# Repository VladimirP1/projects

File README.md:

[Crop whitespace from svgs](https://vladimirp1.github.io/projects/svg-cropper/cropper.html)

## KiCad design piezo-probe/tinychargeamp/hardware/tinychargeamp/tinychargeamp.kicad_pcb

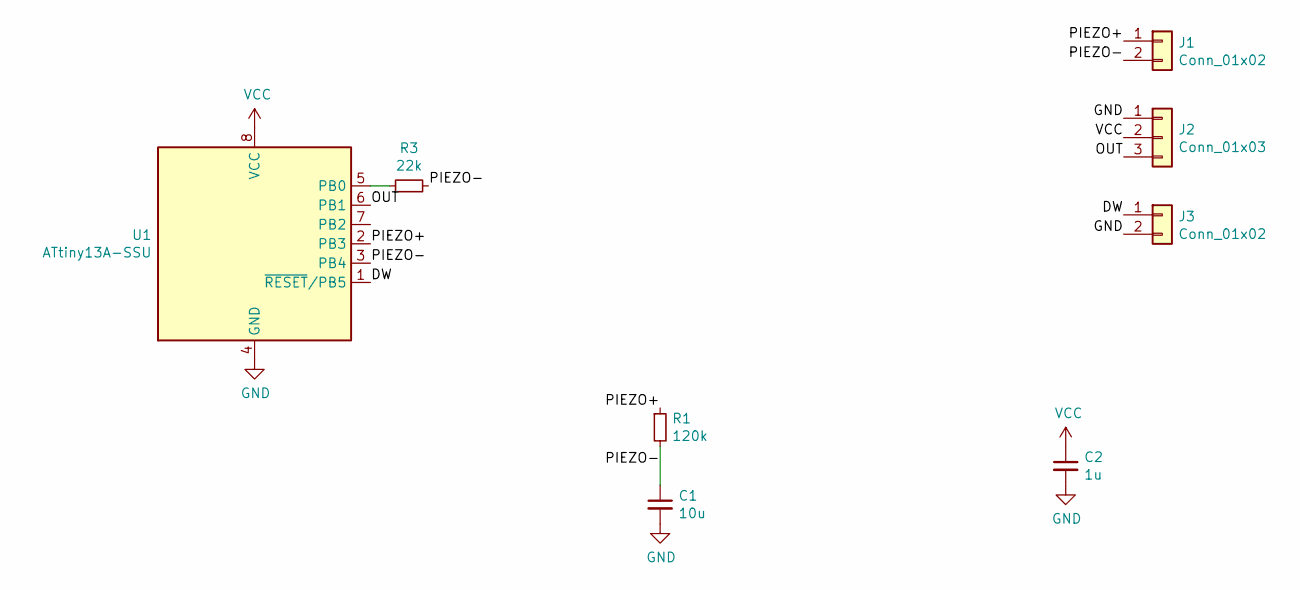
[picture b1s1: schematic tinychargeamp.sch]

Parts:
C1: 10u; C_0805_2012Metric_Pad1.15x1.40mm_HandSolder
C2: 1u; C_0805_2012Metric_Pad1.15x1.40mm_HandSolder
J1, J3: Conn_01x02; edgeconn2
J2: Conn_01x03; edgeconn3
R1: 120k; R_1206_3216Metric_Pad1.42x1.75mm_HandSolder
R3: 22k; R_1206_3216Metric_Pad1.42x1.75mm_HandSolder
U1: ATtiny13A-SSU; SOIC-8_3.9x4.9mm_P1.27mm

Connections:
/DW: J3.1, U1.1 (~RESET~/PB5)
/OUT: J2.3, U1.6 (PB1)
/PIEZO+: J1.1, R1.1, U1.2 (PB3)
/PIEZO-: C1.1, J1.2, R1.2, R3.2, U1.3 (PB4)
GND: C1.2, C2.2, J2.1, J3.2, U1.4 (GND)
unnamed: R3.1, U1.5 (PB0)
VCC: C2.1, J2.2, U1.8 (VCC)

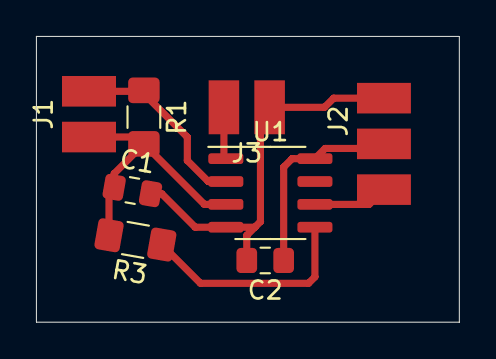
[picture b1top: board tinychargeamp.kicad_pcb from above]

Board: 2 copper layers, 23.5 x 15.9 mm, 8 parts (0 on the bottom side), 7 nets.

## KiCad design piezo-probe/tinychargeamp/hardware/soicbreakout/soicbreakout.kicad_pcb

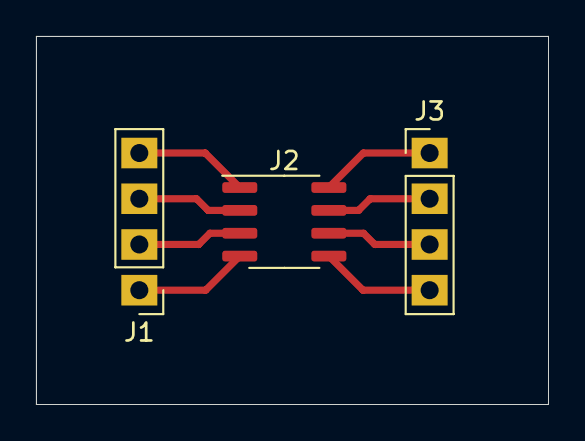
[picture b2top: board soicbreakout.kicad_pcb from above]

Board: 2 copper layers, 28.4 x 20.4 mm, 3 parts (0 on the bottom side), 8 nets.

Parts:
J1, J3: Conn_01x04; PinHeader_1x04_P2.54mm_Vertical_HandSoldering
J2: SOIC8; SOIC-8_3.9x4.9mm_P1.27mm

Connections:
unnamed: J1.1, J2.4
unnamed: J1.2, J2.3
unnamed: J1.3, J2.2
unnamed: J1.4, J2.1
unnamed: J2.5, J3.4
unnamed: J2.6, J3.3
unnamed: J2.7, J3.2
unnamed: J2.8, J3.1

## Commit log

2020-06-06 Add svg-cropper
2020-06-06 Add readme
2020-06-07 Add script to convert svg to png for Photon 3d printer
2020-06-21 Added charge_amp
2020-06-24 Some work on charge amplifiers
2020-06-30 Update board and firmware
2020-06-30 Add piezo holder 3d model.
2020-07-09 tinychargeamp: update for newer piezo mount
2020-07-09 Add some 3d models
2020-07-09 Firmware for repurporsed RC servo
2020-07-10 tinychargeamp: remove division
2020-07-10 tinychargeamp: add a way to configure settings without a PC.
2020-07-20 encoder: start implementing hardware
